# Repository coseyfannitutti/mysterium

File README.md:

# MYSTERIUM
**TKL keyboard that can be entirely assembled using only through hole components, including usb type c**

**[BOM, Build Guide, and Flashing Information](./doc)**

**Kits available at [cftkb.com](https://www.cftkb.com)**

**[Optional High Profile Lasercut Acrylic Case](./case)**

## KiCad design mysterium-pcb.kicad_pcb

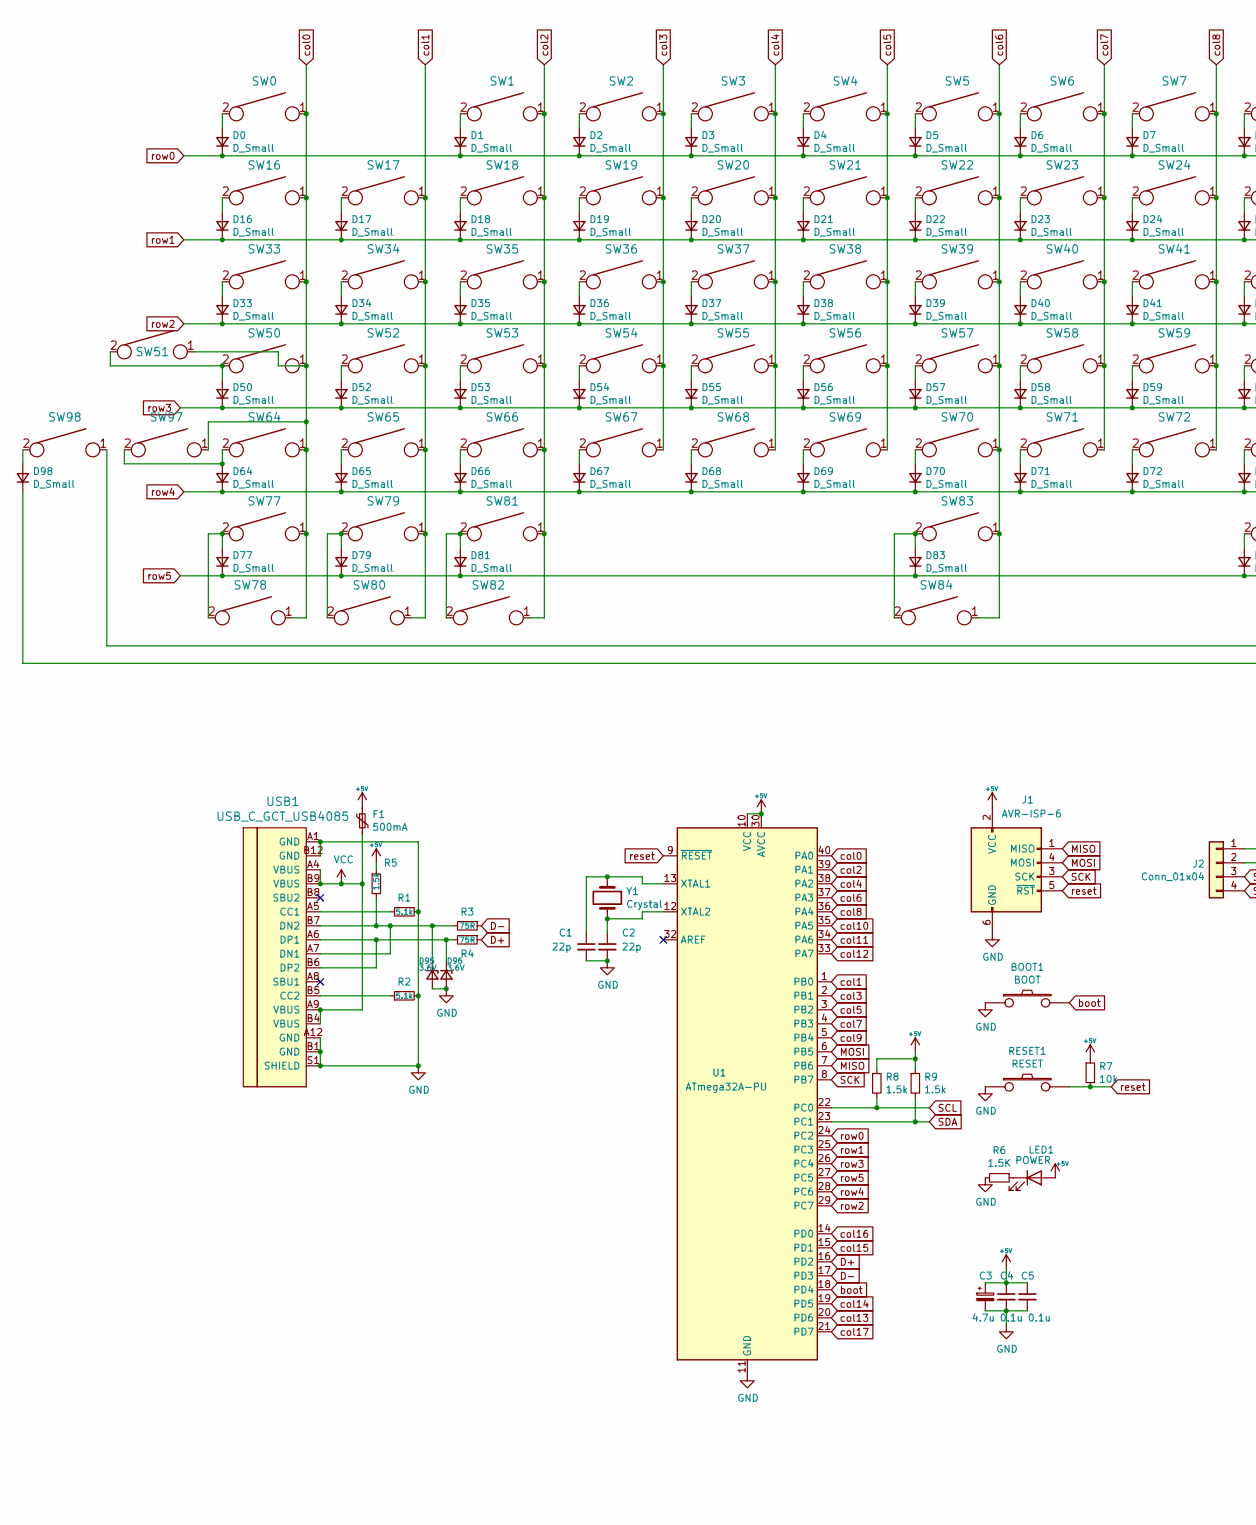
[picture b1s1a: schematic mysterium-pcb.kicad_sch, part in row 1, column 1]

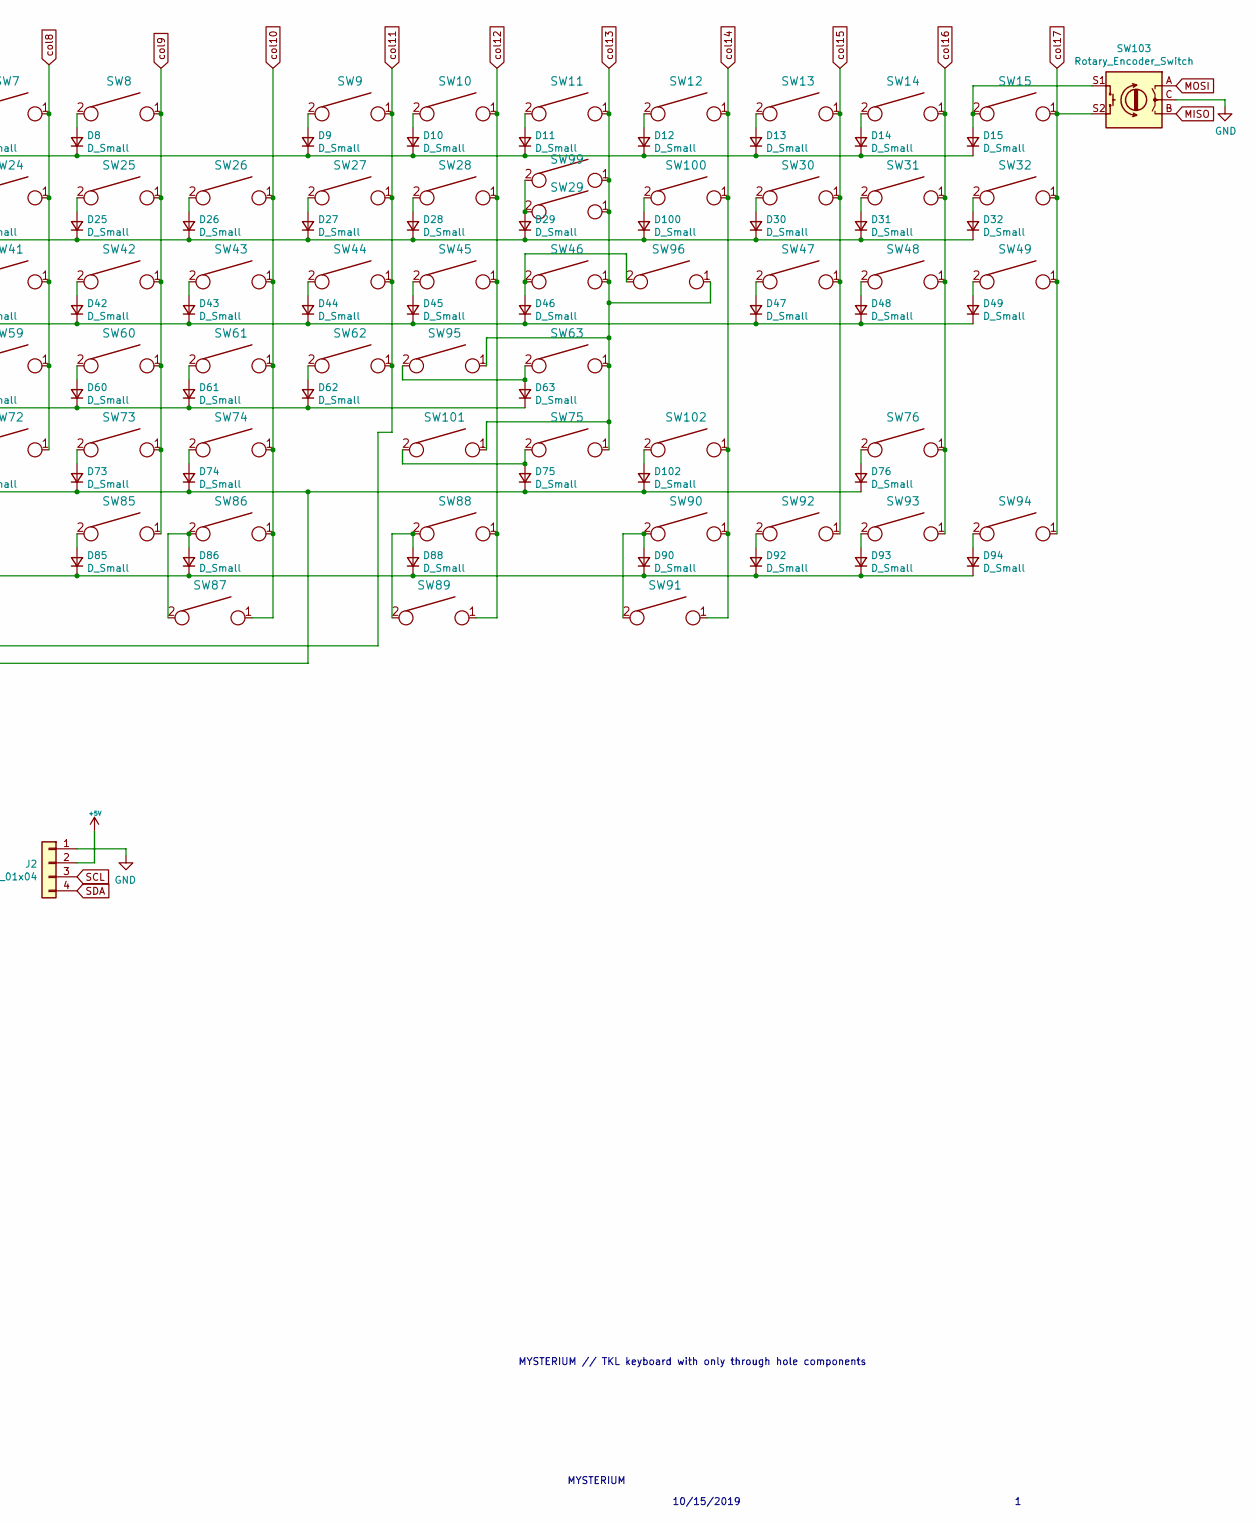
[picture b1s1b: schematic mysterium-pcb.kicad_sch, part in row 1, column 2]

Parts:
BOOT1: BOOT; SW_PUSH_6mm
C1, C2: 22p; C_Disc_D3.0mm_W1.6mm_P2.50mm
C3: 4.7u; CP_Radial_D4.0mm_P1.50mm
C4, C5: 0.1u; C_Disc_D4.3mm_W1.9mm_P5.00mm
D0, D1, D2, D3, D4, D5, D6, D7, D8, D9, D10, D11, D12, D13, D14, D15, D16, D17, D18, D19, D20, D21, D22, D23, D24, D25, D26, D27, D28, D29, D30, D31, D32, D33, D34, D35, D36, D37, D38, D39, D40, D41, D42, D43, D44, D45, D46, D47, D48, D49, D50, D52, D53, D54, D55, D56, D57, D58, D59, D60, D61, D62, D63, D64, D65, D66, D67, D68, D69, D70, D71, D72, D73, D74, D75, D76, D77, D79, D81, D83, D85, D86, D88, D90, D92, D93, D94, D98, D100, D102: D_Small; D_DO-35_SOD27_P5.08mm_Horizontal
D95, D96: 3.6V; D_DO-35_SOD27_P5.08mm_Horizontal
F1: 500mA; polyfuse_5.1mm
J1: AVR-ISP-6; AVR_ICSP_3x2
J2: Conn_01x04; PinHeader_1x04_P2.54mm_Vertical
LED1: POWER; LED_D3.0mm
R1, R2: 5.1k; R_Axial_DIN0204_L3.6mm_D1.6mm_P7.62mm_Horizontal
R3, R4: 75R; R_Axial_DIN0204_L3.6mm_D1.6mm_P7.62mm_Horizontal
R5, R8, R9: 1.5k; R_Axial_DIN0204_L3.6mm_D1.6mm_P7.62mm_Horizontal
R6: 1.5K; R_Axial_DIN0204_L3.6mm_D1.6mm_P7.62mm_Horizontal
R7: 10k; R_Axial_DIN0204_L3.6mm_D1.6mm_P7.62mm_Horizontal
RESET1: RESET; SW_PUSH_6mm
SW0, SW1, SW2, SW3, SW4, SW5, SW6, SW7, SW8, SW9, SW10, SW11, SW12, SW13, SW14, SW15, SW16, SW17, SW18, SW19, SW20, SW21, SW22, SW23, SW24, SW25, SW26, SW27, SW28, SW30, SW31, SW32, SW34, SW35, SW36, SW37, SW38, SW39, SW40, SW41, SW42, SW43, SW44, SW45, SW47, SW48, SW49, SW52, SW53, SW54, SW55, SW56, SW57, SW58, SW59, SW60, SW61, SW62, SW65, SW66, SW67, SW68, SW69, SW70, SW71, SW72, SW73, SW74, SW76, SW80, SW83, SW84, SW89, SW92, SW93, SW94, SW96, SW98, SW99, SW100, SW102: KEYSW; SW_Cherry_MX1A_1.00u_PCB-NOSCREEN
SW29: KEYSW; SW_Cherry_MX1A_2.00u_PCBNOSCREEN
SW33, SW46, SW77, SW81, SW86, SW90: KEYSW; SW_Cherry_MX1A_1.50u_PCBNOSCREEN
SW50, SW101: KEYSW; SW_Cherry_MX1A_1.75u_PCBNOSCREEN
SW51, SW78, SW79, SW82, SW85, SW87, SW88, SW91, SW97: KEYSW; SW_Cherry_MX1A_1.25u_PCBNOSCREEN
SW63, SW64: KEYSW; SW_Cherry_MX1A_2.25u_PCBNOSCREEN
SW75: KEYSW; SW_Cherry_MX1A_2.75u_PCB_NOSCREEN
SW95: KEYSW; SW_Cherry_MX1A_ISOEnter_PCB_ReversedStabilizer
SW103: Rotary_Encoder_Switch; RotaryEncoder_Alps_EC11E-Switch_Vertical_H20mm-for-MX
U1: ATmega32A-PU; DIP-40_W15.24mm
USB1: USB_C_GCT_USB4085
Y1: Crystal; Crystal_HC49-4H_Vertical

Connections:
+5V: C3.1, C4.1, C5.1, F1.1, J1.2 (VCC), J2.2, LED1.2 (A), R5.1, R7.1, R8.1, R9.1, U1.10 (VCC), U1.30 (AVCC)
D+: R4.1, U1.16 (PD2)
D-: R3.1, U1.17 (PD3)
GND: BOOT1.1, C1.2, C2.2, C3.2, C4.2, C5.2, D95.2 (A), D96.2 (A), J1.6 (GND), J2.1, R1.1, R2.2, R6.2, RESET1.1, SW103.C, U1.11 (GND), U1.31 (GND), USB1.A1 (GND), USB1.A12 (GND), USB1.B1 (GND), USB1.B12 (GND), USB1.S1 (SHIELD)
MISO: J1.1 (MISO), SW103.B, U1.7 (PB6)
MOSI: J1.4 (MOSI), SW103.A, U1.6 (PB5)
unnamed: C1.1, U1.13 (XTAL1), Y1.1
unnamed: C2.1, U1.12 (XTAL2), Y1.2
unnamed: D0.2 (A), SW0.2
unnamed: D1.2 (A), SW1.2
unnamed: D2.2 (A), SW2.2
unnamed: D3.2 (A), SW3.2
unnamed: D4.2 (A), SW4.2
unnamed: D5.2 (A), SW5.2
unnamed: D6.2 (A), SW6.2
unnamed: D7.2 (A), SW7.2
unnamed: D8.2 (A), SW8.2
unnamed: D9.2 (A), SW9.2
unnamed: D10.2 (A), SW10.2
unnamed: D11.2 (A), SW11.2
unnamed: D12.2 (A), SW12.2
unnamed: D13.2 (A), SW13.2
unnamed: D14.2 (A), SW14.2
unnamed: D15.2 (A), SW15.2, SW103.S1
unnamed: D16.2 (A), SW16.2
unnamed: D17.2 (A), SW17.2
unnamed: D18.2 (A), SW18.2
unnamed: D19.2 (A), SW19.2
unnamed: D20.2 (A), SW20.2
unnamed: D21.2 (A), SW21.2
unnamed: D22.2 (A), SW22.2
unnamed: D23.2 (A), SW23.2
unnamed: D24.2 (A), SW24.2
unnamed: D25.2 (A), SW25.2
unnamed: D26.2 (A), SW26.2
unnamed: D27.2 (A), SW27.2
unnamed: D28.2 (A), SW28.2
unnamed: D29.2 (A), SW29.2, SW99.2
unnamed: D30.2 (A), SW30.2
unnamed: D31.2 (A), SW31.2
unnamed: D32.2 (A), SW32.2
unnamed: D33.2 (A), SW33.2
unnamed: D34.2 (A), SW34.2
unnamed: D35.2 (A), SW35.2
unnamed: D36.2 (A), SW36.2
unnamed: D37.2 (A), SW37.2
unnamed: D38.2 (A), SW38.2
unnamed: D39.2 (A), SW39.2
unnamed: D40.2 (A), SW40.2
unnamed: D41.2 (A), SW41.2
unnamed: D42.2 (A), SW42.2
unnamed: D43.2 (A), SW43.2
unnamed: D44.2 (A), SW44.2
unnamed: D45.2 (A), SW45.2
unnamed: D46.2 (A), SW46.2, SW96.2
unnamed: D47.2 (A), SW47.2
unnamed: D48.2 (A), SW48.2
unnamed: D49.2 (A), SW49.2
unnamed: D50.2 (A), SW50.2, SW51.2
unnamed: D52.2 (A), SW52.2
unnamed: D53.2 (A), SW53.2
unnamed: D54.2 (A), SW54.2
unnamed: D55.2 (A), SW55.2
unnamed: D56.2 (A), SW56.2
unnamed: D57.2 (A), SW57.2
unnamed: D58.2 (A), SW58.2
unnamed: D59.2 (A), SW59.2
unnamed: D60.2 (A), SW60.2
unnamed: D61.2 (A), SW61.2
unnamed: D62.2 (A), SW62.2
unnamed: D63.2 (A), SW63.2, SW95.2
unnamed: D64.2 (A), SW64.2, SW97.2
unnamed: D65.2 (A), SW65.2
unnamed: D66.2 (A), SW66.2
unnamed: D67.2 (A), SW67.2
unnamed: D68.2 (A), SW68.2
unnamed: D69.2 (A), SW69.2
unnamed: D70.2 (A), SW70.2
unnamed: D71.2 (A), SW71.2
unnamed: D72.2 (A), SW72.2
unnamed: D73.2 (A), SW73.2
unnamed: D74.2 (A), SW74.2
unnamed: D75.2 (A), SW75.2, SW101.2
unnamed: D76.2 (A), SW76.2
unnamed: D77.2 (A), SW77.2, SW78.2
unnamed: D79.2 (A), SW79.2, SW80.2
unnamed: D81.2 (A), SW81.2, SW82.2
unnamed: D83.2 (A), SW83.2, SW84.2
unnamed: D85.2 (A), SW85.2
unnamed: D86.2 (A), SW86.2, SW87.2
unnamed: D88.2 (A), SW88.2, SW89.2
unnamed: D90.2 (A), SW90.2, SW91.2
unnamed: D92.2 (A), SW92.2
unnamed: D93.2 (A), SW93.2
unnamed: D94.2 (A), SW94.2
unnamed: D95.1 (K), R3.2, R5.2, USB1.A7 (DN1), USB1.B7 (DN2)
unnamed: D96.1 (K), R4.2, USB1.A6 (DP1), USB1.B6 (DP2)
unnamed: D98.2 (A), SW98.2
unnamed: D100.2 (A), SW100.2
unnamed: D102.2 (A), SW102.2
unnamed: LED1.1 (K), R6.1
unnamed: R1.2, USB1.A5 (CC1)
unnamed: R2.1, USB1.B5 (CC2)
SCK: J1.3 (SCK), U1.8 (PB7)
SCL: J2.3, R8.2, U1.22 (PC0)
SDA: J2.4, R9.2, U1.23 (PC1)
VCC: F1.2, USB1.A4 (VBUS), USB1.A9 (VBUS), USB1.B4 (VBUS), USB1.B9 (VBUS)
boot: BOOT1.2, U1.18 (PD4)
col0: SW0.1, SW16.1, SW33.1, SW50.1, SW51.1, SW64.1, SW77.1, SW78.1, SW97.1, U1.40 (PA0)
col1: SW17.1, SW34.1, SW52.1, SW65.1, SW79.1, SW80.1, U1.1 (PB0)
col2: SW1.1, SW18.1, SW35.1, SW53.1, SW66.1, SW81.1, SW82.1, U1.39 (PA1)
col3: SW2.1, SW19.1, SW36.1, SW54.1, SW67.1, U1.2 (PB1)
col4: SW3.1, SW20.1, SW37.1, SW55.1, SW68.1, U1.38 (PA2)
col5: SW4.1, SW21.1, SW38.1, SW56.1, SW69.1, U1.3 (PB2)
col6: SW5.1, SW22.1, SW39.1, SW57.1, SW70.1, SW83.1, SW84.1, U1.37 (PA3)
col7: SW6.1, SW23.1, SW40.1, SW58.1, SW71.1, U1.4 (PB3)
col8: SW7.1, SW24.1, SW41.1, SW59.1, SW72.1, U1.36 (PA4)
col9: SW8.1, SW25.1, SW42.1, SW60.1, SW73.1, SW85.1, U1.5 (PB4)
col10: SW26.1, SW43.1, SW61.1, SW74.1, SW86.1, SW87.1, U1.35 (PA5)
col11: SW9.1, SW27.1, SW44.1, SW62.1, SW98.1, U1.34 (PA6)
col12: SW10.1, SW28.1, SW45.1, SW88.1, SW89.1, U1.33 (PA7)
col13: SW11.1, SW29.1, SW46.1, SW63.1, SW75.1, SW95.1, SW96.1, SW99.1, SW101.1, U1.20 (PD6)
col14: SW12.1, SW90.1, SW91.1, SW100.1, SW102.1, U1.19 (PD5)
col15: SW13.1, SW30.1, SW47.1, SW92.1, U1.15 (PD1)
col16: SW14.1, SW31.1, SW48.1, SW76.1, SW93.1, U1.14 (PD0)
col17: SW15.1, SW32.1, SW49.1, SW94.1, SW103.S2, U1.21 (PD7)
reset: J1.5 (~RST), R7.2, RESET1.2, U1.9 (~RESET)
row0: D0.1 (K), D1.1 (K), D2.1 (K), D3.1 (K), D4.1 (K), D5.1 (K), D6.1 (K), D7.1 (K), D8.1 (K), D9.1 (K), D10.1 (K), D11.1 (K), D12.1 (K), D13.1 (K), D14.1 (K), D15.1 (K), U1.24 (PC2)
row1: D16.1 (K), D17.1 (K), D18.1 (K), D19.1 (K), D20.1 (K), D21.1 (K), D22.1 (K), D23.1 (K), D24.1 (K), D25.1 (K), D26.1 (K), D27.1 (K), D28.1 (K), D29.1 (K), D30.1 (K), D31.1 (K), D32.1 (K), D100.1 (K), U1.25 (PC3)
row2: D33.1 (K), D34.1 (K), D35.1 (K), D36.1 (K), D37.1 (K), D38.1 (K), D39.1 (K), D40.1 (K), D41.1 (K), D42.1 (K), D43.1 (K), D44.1 (K), D45.1 (K), D46.1 (K), D47.1 (K), D48.1 (K), D49.1 (K), U1.29 (PC7)
row3: D50.1 (K), D52.1 (K), D53.1 (K), D54.1 (K), D55.1 (K), D56.1 (K), D57.1 (K), D58.1 (K), D59.1 (K), D60.1 (K), D61.1 (K), D62.1 (K), D63.1 (K), U1.26 (PC4)
row4: D64.1 (K), D65.1 (K), D66.1 (K), D67.1 (K), D68.1 (K), D69.1 (K), D70.1 (K), D71.1 (K), D72.1 (K), D73.1 (K), D74.1 (K), D75.1 (K), D76.1 (K), D98.1 (K), D102.1 (K), U1.28 (PC6)
row5: D77.1 (K), D79.1 (K), D81.1 (K), D83.1 (K), D85.1 (K), D86.1 (K), D88.1 (K), D90.1 (K), D92.1 (K), D93.1 (K), D94.1 (K), U1.27 (PC5)

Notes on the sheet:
MYSTERIUM // TKL keyboard with only through hole components
10/15/2019
MYSTERIUM

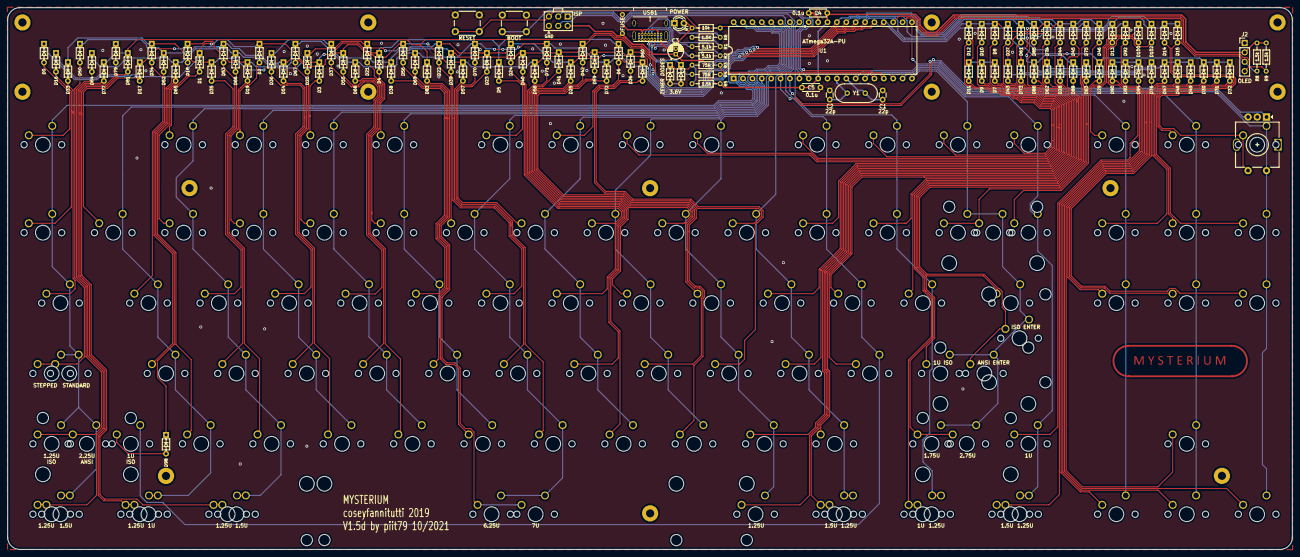
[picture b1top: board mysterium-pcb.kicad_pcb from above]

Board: 2 copper layers, 347.7 x 146.6 mm, 221 parts (0 on the bottom side), 133 nets.

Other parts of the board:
ST83: 6.25U; MX-6.25U-Stabilizer
ST84: 7U; MX-7U-Stabilizer

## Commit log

2019-11-03 Update mysterium-pcb.kicad_pcb-bak
2019-11-04 Update fp-info-cache
2020-01-31 separate standard and winkeyless
2020-04-24 fix scaling
2020-10-04 Created mysterium-top-2_groove.dxf
    added a groove to a copy of mysterium-top-1.dxf; as a replacement for mysterium-top-2.dxf
2020-10-05 Created mysterium-foam-guard.dxf
2021-01-07 Added Small Panels
    Made smaller versions of the acrylic panels so that they can be cut is a generic k40 laser cutter
2021-01-07 Organized small panels
    made folder
2021-01-10 Added a bootloader flashing guide
    Added a section in the bootloader readme that explains the process of flashing the bootloader, setting the fuses, and flashing the keyboard firmware using ArduinoISP and Avrdude
2021-01-10 Fixed indentation
2021-01-10 Added another firmware version
    Grammar is hard
2021-01-11 Reverted All changes made to Readme
2021-01-31 [ImgBot] Optimize images
    *Total -- 12,031.37kb -> 11,200.20kb (6.91%)
    /doc/bootloader/images/example-layer-1.png -- 154.86kb -> 84.99kb (45.12%)
    /doc/bootloader/images/example-layer-0.png -- 177.01kb -> 97.25kb (45.06%)
    /doc/bootloader/images/mysterium-isp-header.png -- 80.35kb -> 44.20kb (44.99%)
    /doc/images/mysterium-kicad.png -- 202.05kb -> 116.31kb (42.43%)
    /doc/images/mysterium-bottom.png -- 179.13kb -> 133.50kb (25.48%)
2021-02-18 fixed link in readme
    link didn't do anything
2021-03-05 Add switch plate files
2021-03-05 Add ISO support
2021-03-29 Add split backspace support
2021-03-29 Remove schematic/PCB backups
2021-03-29 Update gerber files
2021-07-17 Removed duplicate of mysterium-nav-acrylic.dxf (nav-acrylic.dxf in same folder)
2021-12-18 Add support for rotary encoder in the top right position (Pause/Break)
    Gerbers only as source files were overwritten...
2021-12-18 Add support for 0.91" 128x32 OLED display
2022-04-06 Add the build guide to the repository; update PCB image
2022-05-17 Switch to KiCad 6 file formats
2022-05-17 Add foostan/kbd KiCad library as a submodule
2022-06-15 Add ANSI/ISO case plate and foam DXF files
2023-02-22 PCB: add second TRRS socket on the left; use 5.1k I2C pullups
2023-02-22 Fix diode footprints, resolve DRC errors/warnings
2023-02-22 V1.5e: update PCB gerbers
2023-02-22 Add plate (foam) and bottom foam DXF files; add bottom plate project files"
